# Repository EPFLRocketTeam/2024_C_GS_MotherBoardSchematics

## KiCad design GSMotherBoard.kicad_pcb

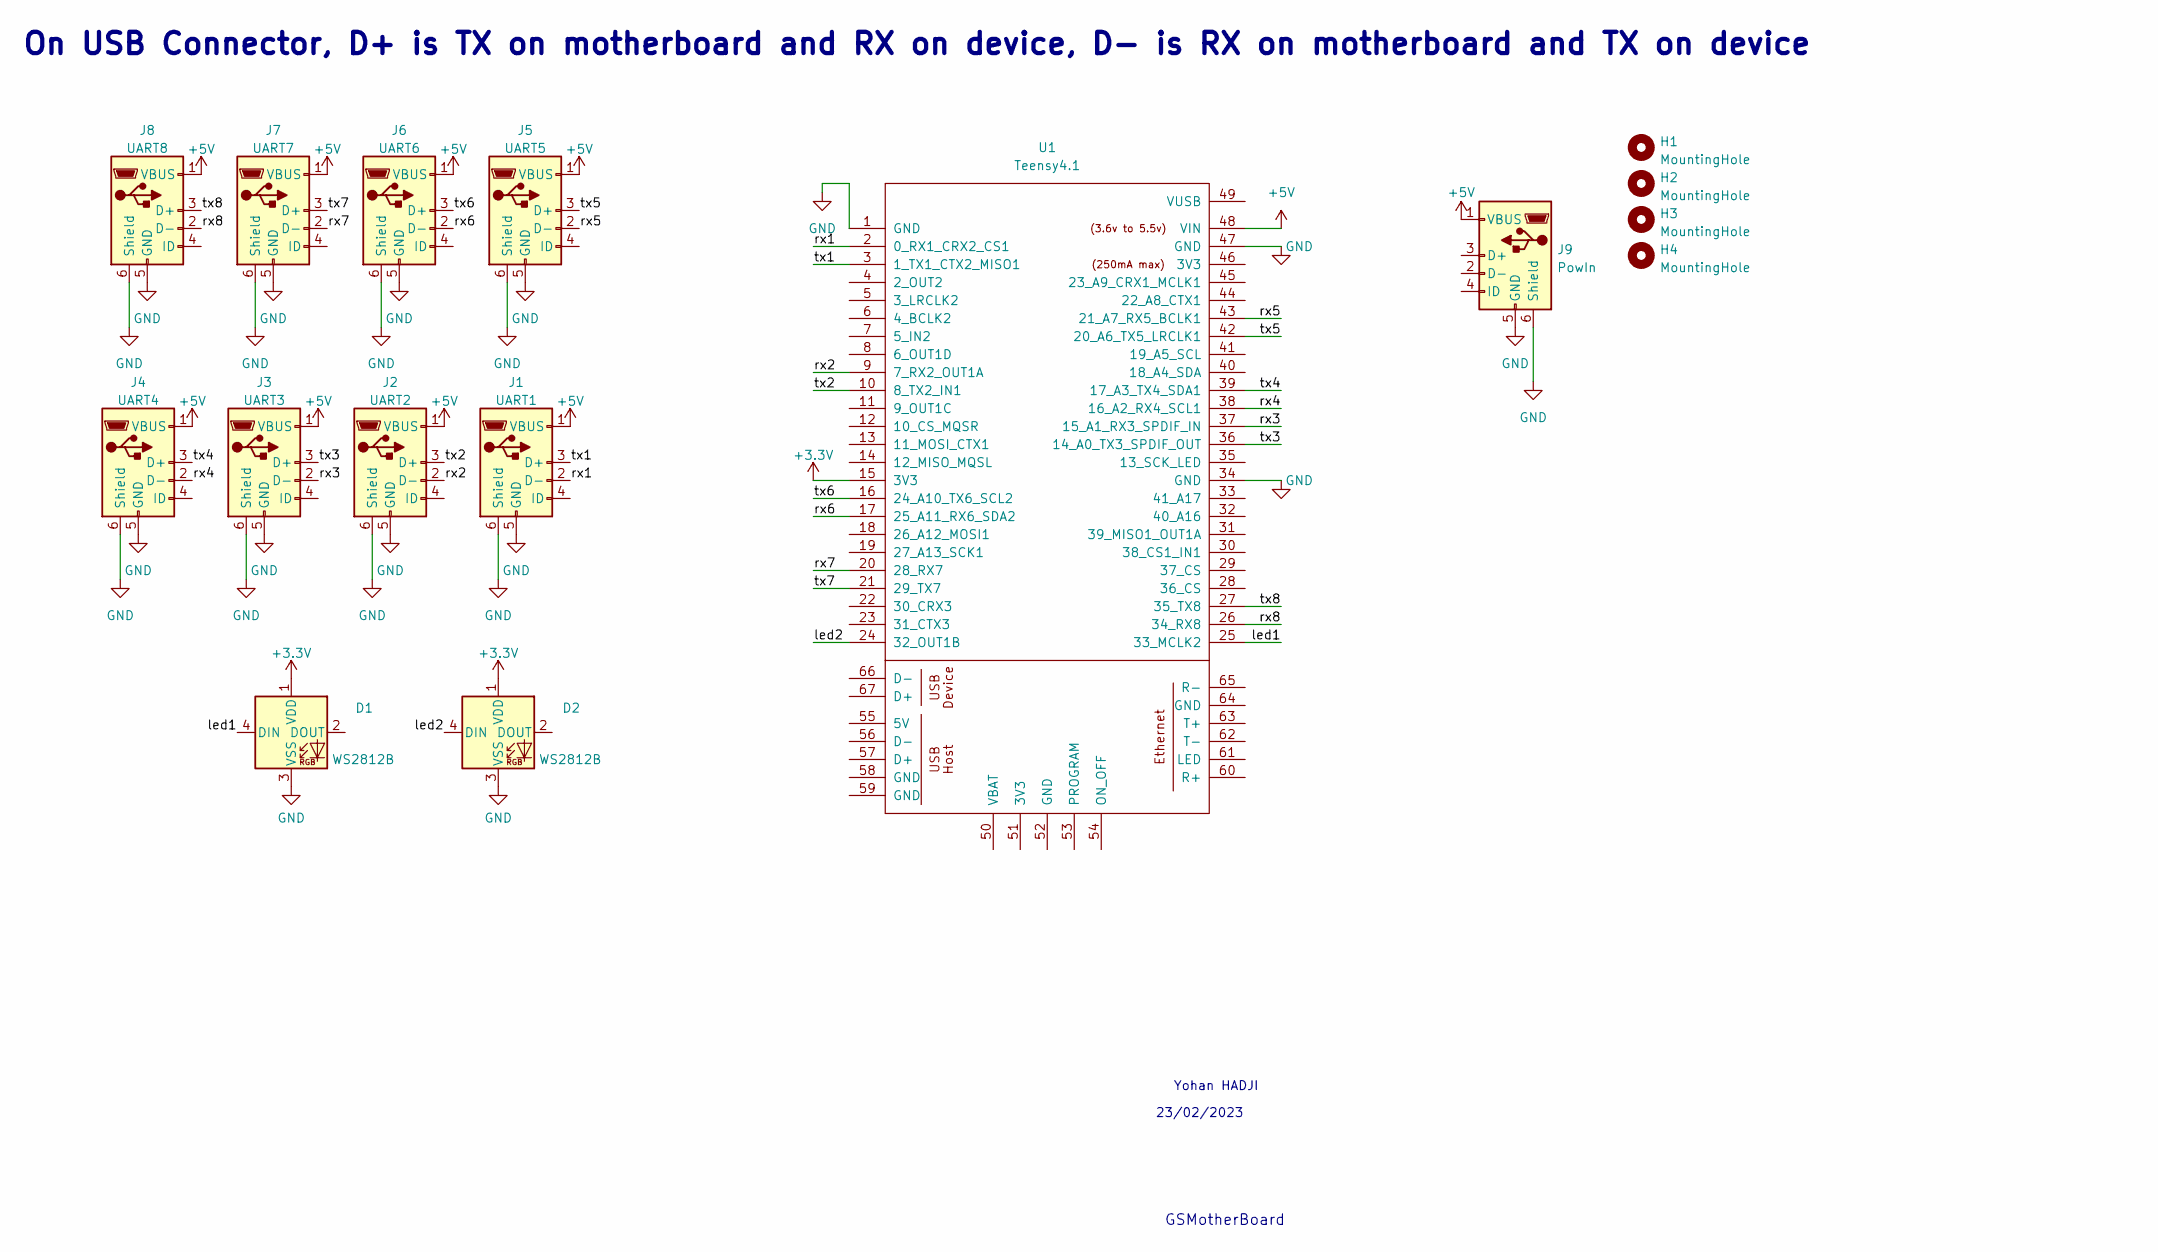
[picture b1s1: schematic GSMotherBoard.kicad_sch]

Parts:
D1, D2: WS2812B; LED_WS2812B_PLCC4_5.0x5.0mm_P3.2mm
H1, H2, H3, H4: MountingHole; MountingHole_3.2mm_M3
J1: UART1; USB_Micro-B_Wuerth_629105150521
J2: UART2; USB_Micro-B_Wuerth_629105150521
J3: UART3; USB_Micro-B_Wuerth_629105150521
J4: UART4; USB_Micro-B_Wuerth_629105150521
J5: UART5; USB_Micro-B_Wuerth_629105150521
J6: UART6; USB_Micro-B_Wuerth_629105150521
J7: UART7; USB_Micro-B_Wuerth_629105150521
J8: UART8; USB_Micro-B_Wuerth_629105150521
J9: PowIn; USB_Micro-B_Wuerth_629105150521
U1: Teensy4.1; Teensy41

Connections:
+3.3V: D1.1 (VDD), D2.1 (VDD), U1.15 (3V3)
+5V: J1.1 (VBUS), J2.1 (VBUS), J3.1 (VBUS), J4.1 (VBUS), J5.1 (VBUS), J6.1 (VBUS), J7.1 (VBUS), J8.1 (VBUS), J9.1 (VBUS), U1.48 (VIN)
/led1: D1.4 (DIN), U1.25 (33_MCLK2)
/led2: D2.4 (DIN), U1.24 (32_OUT1B)
/rx1: J1.2 (D-), U1.2 (0_RX1_CRX2_CS1)
/rx2: J2.2 (D-), U1.9 (7_RX2_OUT1A)
/rx3: J3.2 (D-), U1.37 (15_A1_RX3_SPDIF_IN)
/rx4: J4.2 (D-), U1.38 (16_A2_RX4_SCL1)
/rx5: J5.2 (D-), U1.43 (21_A7_RX5_BCLK1)
/rx6: J6.2 (D-), U1.17 (25_A11_RX6_SDA2)
/rx7: J7.2 (D-), U1.20 (28_RX7)
/rx8: J8.2 (D-), U1.26 (34_RX8)
/tx1: J1.3 (D+), U1.3 (1_TX1_CTX2_MISO1)
/tx2: J2.3 (D+), U1.10 (8_TX2_IN1)
/tx3: J3.3 (D+), U1.36 (14_A0_TX3_SPDIF_OUT)
/tx4: J4.3 (D+), U1.39 (17_A3_TX4_SDA1)
/tx5: J5.3 (D+), U1.42 (20_A6_TX5_LRCLK1)
/tx6: J6.3 (D+), U1.16 (24_A10_TX6_SCL2)
/tx7: J7.3 (D+), U1.21 (29_TX7)
/tx8: J8.3 (D+), U1.27 (35_TX8)
GND: D1.3 (VSS), D2.3 (VSS), J1.5 (GND), J1.6 (Shield), J2.5 (GND), J2.6 (Shield), J3.5 (GND), J3.6 (Shield), J4.5 (GND), J4.6 (Shield), J5.5 (GND), J5.6 (Shield), J6.5 (GND), J6.6 (Shield), J7.5 (GND), J7.6 (Shield), J8.5 (GND), J8.6 (Shield), J9.5 (GND), J9.6 (Shield), U1.1 (GND), U1.34 (GND), U1.47 (GND)

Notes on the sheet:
Yohan HADJI
23/02/2023
On USB Connector, D+ is TX on motherboard and RX on device, D- is RX on motherboard and TX on device
GSMotherBoard

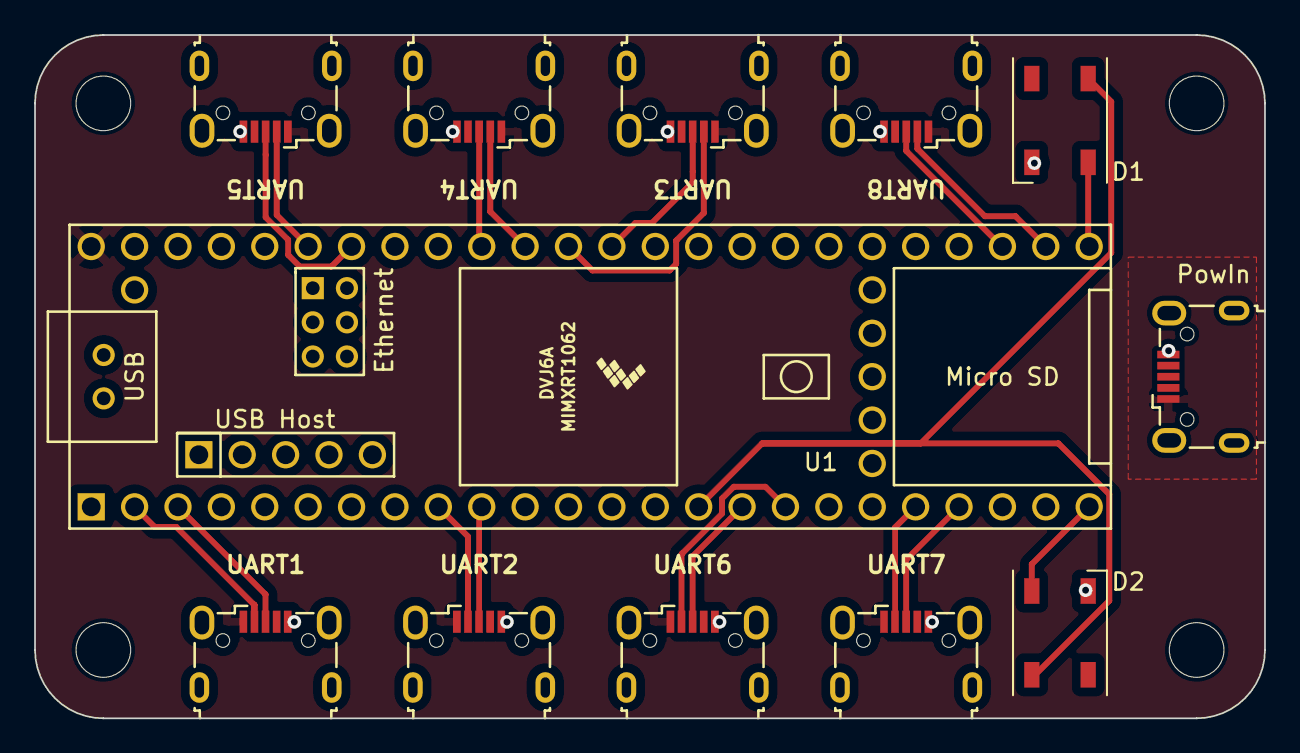
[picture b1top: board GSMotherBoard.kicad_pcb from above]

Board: 2 copper layers, 72.0 x 40.0 mm, 16 parts (0 on the bottom side), 21 nets.

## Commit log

2024-09-07 update to kicad 8
